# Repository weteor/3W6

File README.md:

# 3w6 - split ortholinear keyboard

The 3w6 is a low profile, split ortholinear keyboard with 36 keys.

I needed a keyboard for work and wasn't really satisfied with the available alternatives (namely Corne, Kyria and Ferris), mostly because they were rather large and didn't had the spacing I would like.

It's designed to be a no frills, cheap and small keyboard to be taken everywhere.

So no hotswap, no multiple switchtypes, no encoders, no LEDs.

BUT with onboard controllers (so no extra ProMicros, Elite-C), production files including SMT assembly files, and sturdy through hole mounted USB-C connectors.
## revision 2.2
changes:
- combi footprint to be able to use the AU or MU variant of the AtMega32U4. 
- add BOM files for each AU and MU variant, so you can choose the cheaper one.
## revision 2
changes:
- new middle plate (1.6mm, better 2.0mm) instead of diodes. Uses Aluminium PCBs as a cheaper alternative to lasered aluminium. 
- pimoroni trackball support (can only be used combined with the new middle plate when used with the plate)
- plate is now 1.2mm thick, to fit the chocs better. Needs middle plate, since the cutouts of the USB-Connectors were left out. There is enough space for them under the plate, when the middle plate is in place.
- added mounting holes to support tenting puck from splitkb.com. Due to insufficient space not all 4 holes are supported, but 3 screws should be enough to hold everything comfortably in position. Can only be used plateless! 
- package for the MCU was changed from QFN44 to TQFP44, since the previous one wasn't available. Can now be soldered/replaced by hand if need.
- IO-expander was changed from TCA9555RTWR to TCA9555PWR (alternativly PCA9555PW), since the previous one wasn't available. Package changed from WQFN24 to TSSOP24. Can now be soldered/replaced by hand if need.
- Board can now be soldered by hand if needed (challenging though, 0402 components). 

## try it
You may also compare the layout with other layouts of other layouts at https://jhelvy.shinyapps.io/splitkbcompare/ .

Or you can print [this file](https://raw.githubusercontent.com/weteor/3W6/main/plate_outline.pdf) to test if you like the layout. Or mount it to some cardboard and test it with your favourite switches.

## production files
If you want to build one yourself, grab the 
Gerber files [here](https://github.com/weteor/3W6/tree/main/prod/Rev2) and give it a go.

And if 3d printing is your thing, files for plate and midlayer can be found [here](https://github.com/weteor/3W6/tree/main/prod/Rev2/3d%20Print) (made by the great [bomtarnes](https://github.com/keyboard-magpie), thanks a lot!)
## build instructions
you may find instructions here: 
- rev1 (deprecated): [build instructions rev1](./prod/build_instruction_rev1.md)
- **rev2 (current)**   : [build instructions rev2](./prod/build_instruction_rev2.md)

## firmware
This keyboard uses [QMK firmware](https://qmk.fm/).
You can find everything you need to build a firmware for this board in the [QMK Repository](https://github.com/qmk/qmk_firmware). 

Here are some instructions on how to [set up your QMK environment](https://docs.qmk.fm/#/newbs) and a few notes [specifically for the 3w6](https://github.com/qmk/qmk_firmware/tree/master/keyboards/3w6).

## the rest
Everything in this repository is free to use however you might see fit. If you want to support me and my projects, please consider linking back to this repository if you build/change/use anything. 

If you would like to send me a tip, you could do it [here](https://ko-fi.com/weteor) (Please don't feel like you have to).

## rev2(current)

## rev1

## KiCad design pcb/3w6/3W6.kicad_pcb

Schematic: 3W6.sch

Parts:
C1, C2: 22pF; C_0402_HandSolder
C3, C4, C5, C6, C7: 0.1uF; C_0402_HandSolder
C8: 4.7uF; C_0402_HandSolder
C9: 1uF; C_0402_HandSolder
D2, D3, D4, D5, D6, D7, D8, D9, D10, D11, D12, D13, D14, D15, D16, D17, D18, D19, D20, D21, D22, D23, D24, D25, D26, D27, D28, D29, D30, D31, D32, D33, D34, D35, D36, D37, D40, D43, D44, D50, D52: D; D_SOD-123
F1: 500mA; Fuse_1206_3216Metric
J1: USB_C Main; USB-C-12-Pin-MidMount
J2: USB_C I2C_L; USB-C-12-Pin-MidMount
J3: USB_C I2C_R; USB-C-12-Pin-MidMount
R1, R2: 5.1k; R_0402_HandSolder
R3, R4: 4.7k; R_0402_HandSolder
R5, R8, R9: 10k; R_0402_HandSolder
R6, R7: 22R; R_0402_HandSolder
SW1: SW_Push; Micro_Push_Button_3x6x2.5mm
SW2, SW3, SW4, SW5, SW6, SW7, SW8, SW9, SW10, SW11, SW12, SW13, SW14, SW15, SW16, SW18, SW19, SW20, SW21, SW22, SW23, SW24, SW25, SW26, SW27, SW28, SW29, SW30, SW31, SW32, SW34, SW35, SW36: SW_Push; Kailh_Choc_1u
SW17: Trackball_Choc_Combi; trackball_choc_combi
SW33, SW37: SW_Push; Kailh_Choc_1.5u
U1: ATmega32U4-AU; TQFP-44_10x10mm_P0.8mm
U2: PCA9555PW; TSSOP-24_4.4x7.8mm_P0.65mm
Y1: 16MHZ; Crystal_SMD_3225-4Pin_3.2x2.5mm

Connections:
+5V: C4.2, C5.2, C6.2, C7.2, C8.2, F1.2, J2.A4 (VBUS), J2.A9 (VBUS), J2.B4 (VBUS), J2.B9 (VBUS), R3.1, R4.1, R8.1, U1.2, U1.7, U1.14, U1.24, U1.34, U1.44
/Col_L0: SW5.1, SW6.1, SW7.1, U1.11
/Col_L1: SW11.1, SW12.1, SW13.1, U1.1
/Col_L2: SW18.1, SW19.1, SW20.1, SW21.1, U1.36
/Col_L3: SW26.1, SW27.1, SW28.1, SW29.1, U1.30
/Col_L4: SW34.1, SW35.1, SW36.1, SW37.1, U1.29
/Col_R0: SW2.1, SW3.1, SW4.1, U2.4 (IO0_0)
/Col_R1: SW8.1, SW9.1, SW10.1, U2.5 (IO0_1)
/Col_R2: SW14.1, SW15.1, SW16.1, SW17.1, U2.6 (IO0_2)
/Col_R3: SW22.1, SW23.1, SW24.1, SW25.1, U2.7 (IO0_3)
/Col_R4: SW30.1, SW31.1, SW32.1, SW33.1, U2.8 (IO0_4)
/D+: R7.1, U1.4
/D-: R6.1, U1.3
/I2C_SCL_L: J2.A6 (D+), J2.B6 (D+), R4.2, U1.18
/I2C_SCL_R: J3.A6 (D+), J3.B6 (D+), SW17.SCL, U2.22 (SCL)
/I2C_SDA_L: J2.A7 (D-), J2.B7 (D-), R3.2, U1.19
/I2C_SDA_R: J3.A7 (D-), J3.B7 (D-), SW17.SDA, U2.23 (SDA)
/Row_L0: D5.1 (K), D11.1 (K), D18.1 (K), D26.1 (K), D34.1 (K), U1.8
/Row_L1: D6.1 (K), D12.1 (K), D19.1 (K), D27.1 (K), D35.1 (K), U1.9
/Row_L2: D7.1 (K), D13.1 (K), D20.1 (K), D28.1 (K), D36.1 (K), U1.10
/Row_L3: D21.1 (K), D29.1 (K), D37.1 (K), U1.28
/Row_R0: D2.1 (K), D8.1 (K), D14.1 (K), D22.1 (K), D30.1 (K), U2.13 (IO1_0)
/Row_R1: D3.1 (K), D9.1 (K), D15.1 (K), D23.1 (K), D31.1 (K), U2.14 (IO1_1)
/Row_R2: D4.1 (K), D10.1 (K), D16.1 (K), D24.1 (K), D32.1 (K), U2.15 (IO1_2)
/Row_R3: D17.1 (K), D25.1 (K), D33.1 (K), U2.16 (IO1_3)
GND: C1.2, C2.2, C4.1, C5.1, C6.1, C7.1, C8.1, C9.2, J1.A1 (GND), J1.A12 (GND), J1.B1 (GND), J1.B12 (GND), J2.A1 (GND), J2.A12 (GND), J2.B1 (GND), J2.B12 (GND), R1.2, R2.2, R9.1, SW1.1, U1.5, U1.15, U1.23, U1.35, U1.43, Y1.2, Y1.4
unnamed: C1.1, U1.17, Y1.1
unnamed: C2.1, U1.16, Y1.3
unnamed: C9.1, U1.6
unnamed: D2.2 (A), SW2.2
unnamed: D3.2 (A), SW3.2
unnamed: D4.2 (A), SW4.2
unnamed: D5.2 (A), SW5.2
unnamed: D6.2 (A), SW6.2
unnamed: D7.2 (A), SW7.2
unnamed: D8.2 (A), SW8.2
unnamed: D9.2 (A), SW9.2
unnamed: D10.2 (A), SW10.2
unnamed: D11.2 (A), SW11.2
unnamed: D12.2 (A), SW12.2
unnamed: D13.2 (A), SW13.2
unnamed: D14.2 (A), SW14.2
unnamed: D15.2 (A), SW15.2
unnamed: D16.2 (A), SW16.2
unnamed: D17.2 (A), SW17.2
unnamed: D18.2 (A), SW18.2
unnamed: D19.2 (A), SW19.2
unnamed: D20.2 (A), SW20.2
unnamed: D21.2 (A), SW21.2
unnamed: D22.2 (A), SW22.2
unnamed: D23.2 (A), SW23.2
unnamed: D24.2 (A), SW24.2
unnamed: D25.2 (A), SW25.2
unnamed: D26.2 (A), SW26.2
unnamed: D27.2 (A), SW27.2
unnamed: D28.2 (A), SW28.2
unnamed: D29.2 (A), SW29.2
unnamed: D30.2 (A), SW30.2
unnamed: D31.2 (A), SW31.2
unnamed: D32.2 (A), SW32.2
unnamed: D33.2 (A), SW33.2
unnamed: D34.2 (A), SW34.2
unnamed: D35.2 (A), SW35.2
unnamed: D36.2 (A), SW36.2
unnamed: D37.2 (A), SW37.2
unnamed: F1.1, J1.A4 (VBUS), J1.A9 (VBUS), J1.B4 (VBUS), J1.B9 (VBUS)
unnamed: J1.A5 (CC1), R1.1
unnamed: J1.A6 (D+), J1.B6 (D+), R7.2
unnamed: J1.A7 (D-), J1.B7 (D-), R6.2
unnamed: J1.B5 (CC2), R2.1
unnamed: R5.2, U2.1 (~INT)
unnamed: R8.2, SW1.2, U1.13
unnamed: R9.2, U1.33
VDD: C3.2, J3.A4 (VBUS), J3.A9 (VBUS), J3.B4 (VBUS), J3.B9 (VBUS), R5.1, SW17.VCC, U2.24 (VDD)
VSS: C3.1, J3.A1 (GND), J3.A12 (GND), J3.B1 (GND), J3.B12 (GND), SW17.GND, U2.2 (A1), U2.3 (A2), U2.12 (VSS), U2.21 (A0)

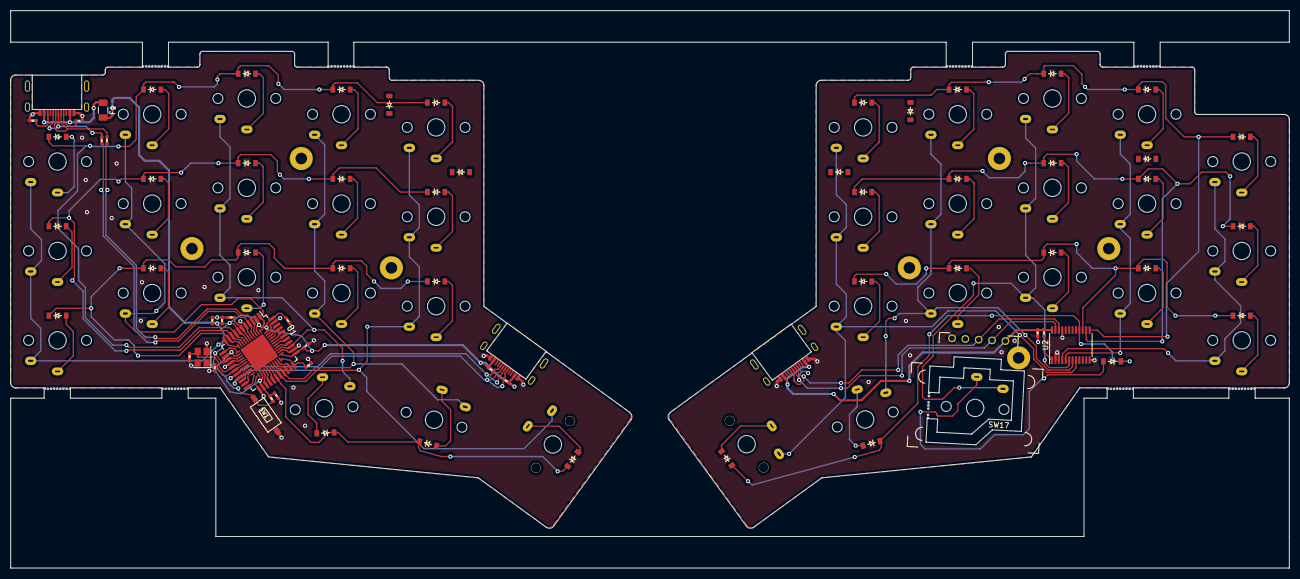
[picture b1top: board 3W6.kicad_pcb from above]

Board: 2 copper layers, 243.2 x 106.0 mm, 103 parts (0 on the bottom side), 75 nets.

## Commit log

2021-03-07 add: inkscape files with possible outlines
2021-03-18 new possible outlines
2021-03-18 Add: pinout picture for USB-C 16pin
2021-03-18 add: parametric Freecad-Model for the plate/outline
2021-03-20 Add: DXF Board Outlines
2021-03-20 Add: USB connector data sheet
2021-03-20 Add: KiCad Files + First Schematic
2021-03-21 outline.dxf for left/right pcb
2021-03-21 pcb wip
2021-03-21 clean up outline files
2021-03-22 PCB finished
2021-03-22 rename
2021-03-23 Add: Plate PCB
2021-06-08 fixing some outlines
2021-06-08 add production files (bom might not be valid)
2021-06-15 add preliminary keymaps
2021-06-15 fix cfg layer
2021-06-15 add readme.md for keymap
2021-06-15 fix readme.md
2021-06-15 add finished board
2021-06-15 change size of board image
2021-06-20 add outline file for switchplate
2021-06-21 new pcb file structure
2021-06-21 add part library
2021-06-21 fix library paths to use included part library fix wrong value for crystal condensators
2021-06-25 new images
2021-06-28 add footprint for pimoroni trackball
2021-06-29 add: symbol and footprint for trackball/switch combination
2021-06-29 add: Pimoroni Trackball support
2021-06-29 chg: plate to match pcb after trackball support
2021-06-29 chg: uses atmega32u4-AU now
2021-06-30 add: middle plate chg: rerouting whole board, to eliminate traces under middle plate chg: repositioning components to get a higher clearance in case an aluminium or steel middle plate is used.
2021-07-01 fix middle plate outlines right half
2021-07-01 chg: new io-expander (TCA9535), change package to TSSOP-24
2021-07-04 Create LICENSE
2021-07-04 making files ready for production
2021-07-04 adding single files for alu middle plate sides
2021-07-09 changes for production
2021-07-09 update production files
2021-07-09 add support for tenting puck
2021-07-27 move images
2021-07-28 fix problems from last production run
    changed IO-Expander to PCA9555
    moved some vias to connect the copper island around the pimoroni GND pin to board GND
2021-07-28 adding corrected production files
2021-07-28 increased version no to 2.1 to distinguish boards from different runs/changes
2021-07-28 better rev2 images
2021-08-19 add 3d printing files by bomtarnes
2021-10-14 Update README.md
    Corrected MCU package to TQFP44, to minimize my own confusion.
2022-01-26 cleanup
2022-05-07 Added tenting_base 12deg & construction file
2022-10-18 add combie footprint for atmega. Can be used with MU and AU variant
2022-10-18 Add updated production files
2022-10-18 add parts to library

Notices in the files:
pcb/3w6/3W6.kicad_pcb:
(c)weteor :: github.com/weteor/3W6 :: CERN-OHL-P v2
pcb/3w6/3W6.sch:
Licensed under CERN-OHL-P v2
